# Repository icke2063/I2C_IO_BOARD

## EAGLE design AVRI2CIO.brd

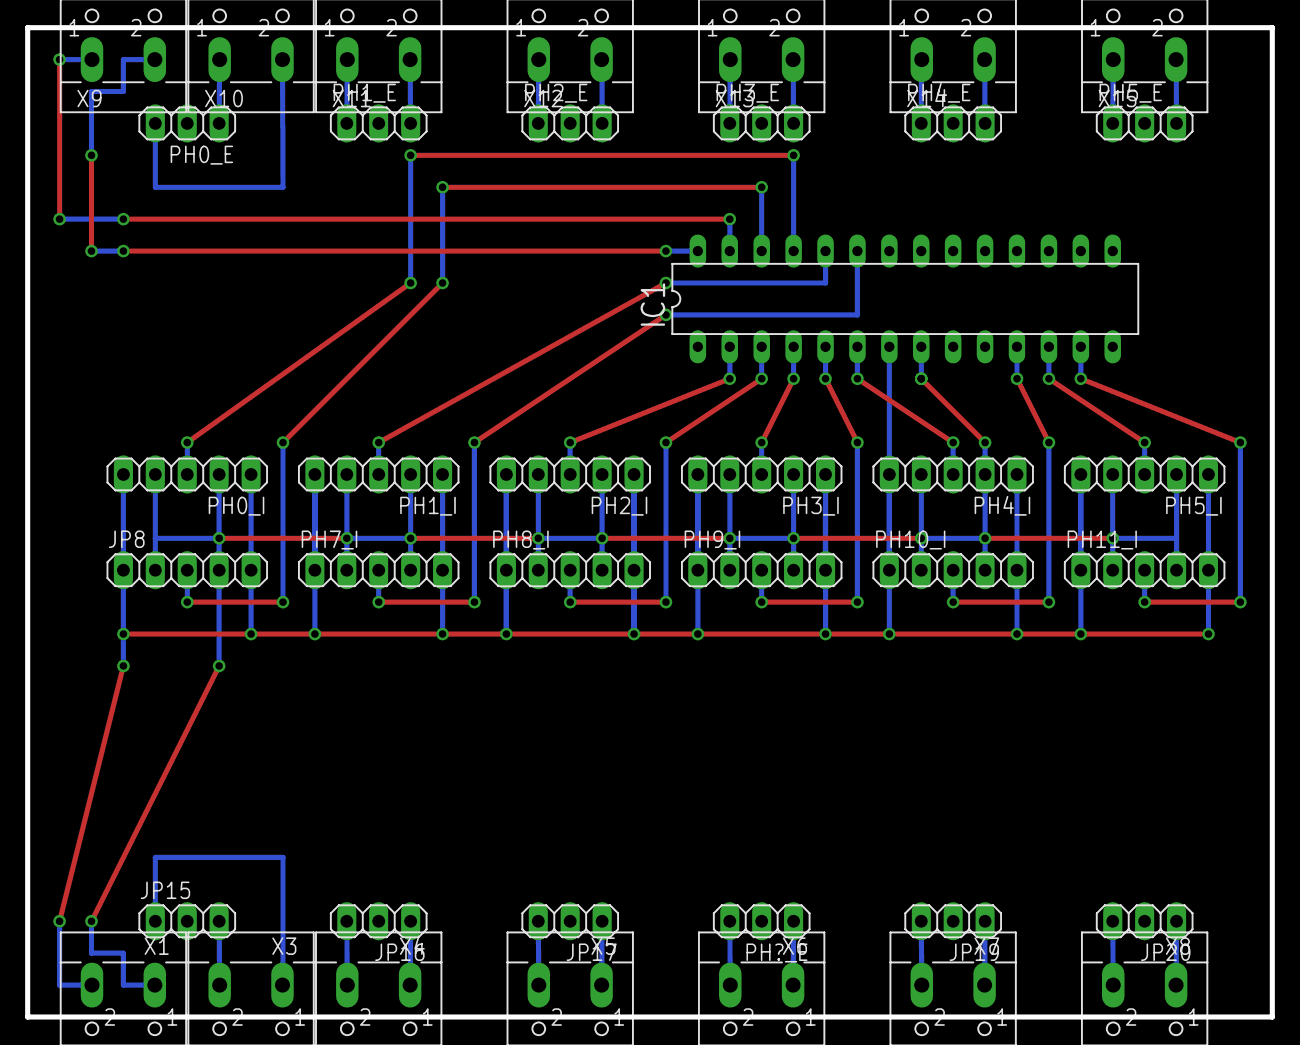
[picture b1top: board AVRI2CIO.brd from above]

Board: 2 copper layers, 99.1 x 78.7 mm, 39 parts (0 on the bottom side), 40 nets.

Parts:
IC1: MEGA8-P; DIL28-3
JP8: 1X05
JP15, JP16, JP17, JP19, JP20: 1X03
PH0_E, PH1_E, PH2_E, PH3_E, PH4_E, PH5_E: 1X03
PH0_I, PH1_I, PH2_I, PH3_I, PH4_I, PH5_I, PH7_I, PH8_I, PH9_I, PH10_I, PH11_I: 1X05
PH?_E: 1X03
X1, X3, X4, X5, X6, X7, X8, X9, X10, X11, X12, X13, X14, X15: W237-102

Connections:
+5V: IC1.7, JP8.1, JP8.5, PH0_I.1, PH0_I.5, PH1_I.1, PH1_I.5, PH2_I.1, PH2_I.5, PH3_I.1, PH3_I.5, PH4_I.1, PH4_I.5, PH5_I.1, PH5_I.5, PH7_I.1, PH7_I.5, PH8_I.1, PH8_I.5, PH9_I.1, PH9_I.5, PH10_I.1, PH10_I.5, PH11_I.1, PH11_I.5, X1.2
GND: IC1.8, JP8.2, JP8.4, PH0_I.2, PH0_I.4, PH1_I.2, PH1_I.4, PH2_I.2, PH2_I.4, PH3_I.2, PH3_I.4, PH4_I.2, PH4_I.4, PH5_I.2, PH5_I.4, PH7_I.2, PH7_I.4, PH8_I.2, PH8_I.4, PH9_I.2, PH9_I.4, PH10_I.2, PH10_I.4, PH11_I.2, PH11_I.4, X1.1
unnamed: PH0_E.3, X10.2
unnamed: JP15.3, X3.2
unnamed: JP15.1, X3.1
unnamed: JP16.3, X4.2
unnamed: JP16.1, X4.1
unnamed: JP17.3, X5.2
unnamed: JP17.1, X5.1
unnamed: PH?_E.3, X6.2
unnamed: PH?_E.1, X6.1
unnamed: JP19.3, X7.2
unnamed: JP19.1, X7.1
unnamed: JP20.3, X8.2
unnamed: JP20.1, X8.1
unnamed: PH0_E.1, X10.1
unnamed: PH1_E.1, X11.1
unnamed: PH1_E.3, X11.2
unnamed: PH2_E.1, X12.1
unnamed: PH2_E.3, X12.2
unnamed: PH3_E.1, X13.1
unnamed: PH3_E.3, X13.2
unnamed: PH4_E.1, X14.1
unnamed: PH4_E.3, X14.2
unnamed: PH5_E.1, X15.1
unnamed: PH5_E.3, X15.2
PC0: IC1.23, PH7_I.3
PC1: IC1.24, PH1_I.3
PC2: IC1.25, PH0_I.3
PC3: IC1.26, JP8.3
PD0: IC1.2, PH2_I.3
PD1: IC1.3, PH8_I.3
PD2: IC1.4, PH3_I.3
PD3: IC1.5, PH9_I.3
PD4: IC1.6, PH4_I.3
PD5: IC1.11, PH10_I.3
PD6: IC1.12, PH5_I.3
PD7: IC1.13, PH11_I.3
SCL: IC1.28, X9.2
SDA: IC1.27, X9.1

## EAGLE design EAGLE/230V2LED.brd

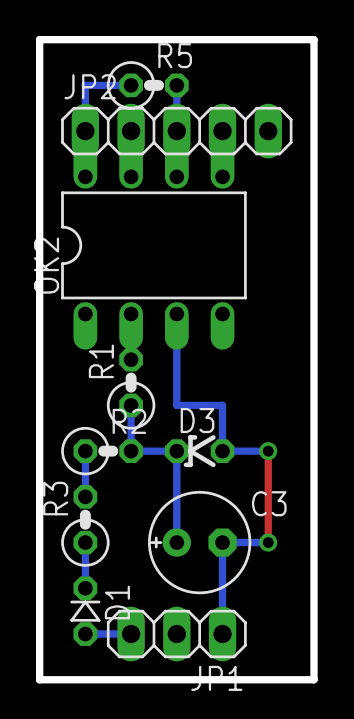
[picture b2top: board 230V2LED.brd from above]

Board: 2 copper layers, 15.2 x 35.6 mm, 10 parts (0 on the bottom side), 9 nets.

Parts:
C3: E2,5-6E
D1: D-2.5
D3: ZDIO-2.5
JP1: 1X03
JP2: 1X05
OK2: 6N138; DIL08
R1: 12K; 0207/2V
R2, R3: 22K; 0207/2V
R5: 0207/2V

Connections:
unnamed: JP2.1, OK2.8, R5.1
unnamed: JP2.4, OK2.5
unnamed: JP2.3, OK2.6, R5.2
unnamed: D1.C, R3.1
unnamed: R2.1, R3.2
unnamed: OK2.2, R1.2
unnamed: D1.A, JP1.3
unnamed: C3.-, D3.A, JP1.1, OK2.3
unnamed: C3.+, D3.C, R1.1, R2.2

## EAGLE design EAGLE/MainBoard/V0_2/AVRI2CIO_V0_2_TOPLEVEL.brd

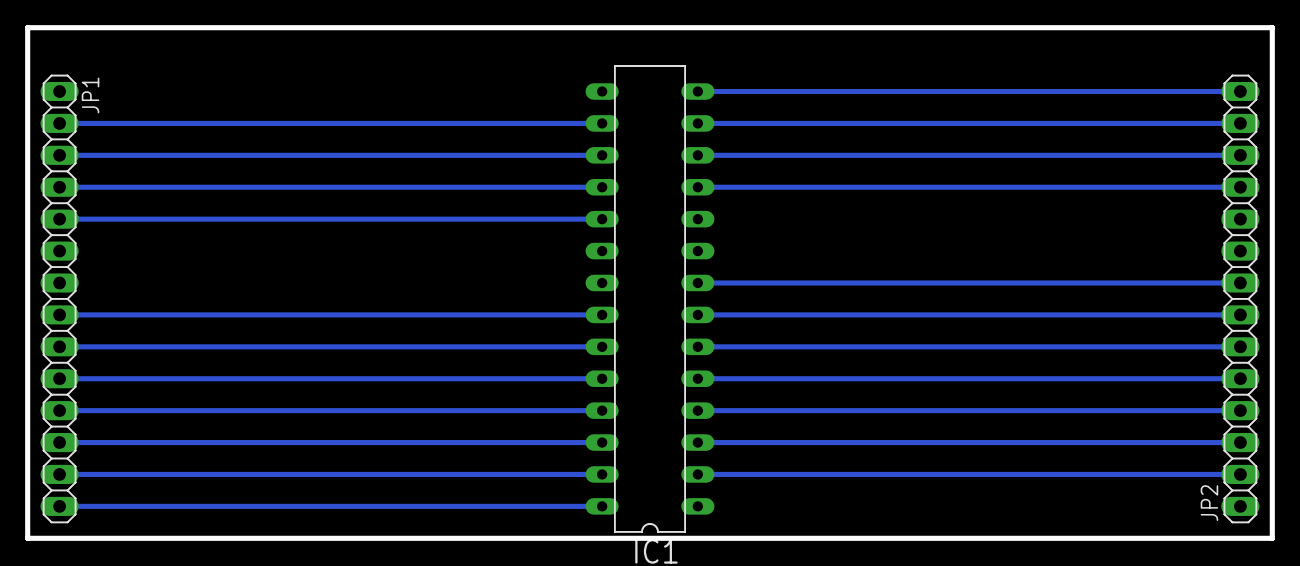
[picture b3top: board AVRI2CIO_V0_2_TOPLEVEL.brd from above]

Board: 2 copper layers, 99.1 x 40.6 mm, 3 parts (0 on the bottom side), 21 nets.

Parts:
IC1: MEGA8-P; DIL28-3
JP1, JP2: 1X14

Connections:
+5V: IC1.7, JP2.7
GND: IC1.8, IC1.22, JP1.8, JP2.8
PB0: IC1.14, JP2.14
PB2: IC1.16, JP1.2
PB3: IC1.17, JP1.3
PB4: IC1.18, JP1.4
PB5: IC1.19, JP1.5
PC0: IC1.23, JP1.9
PC1: IC1.24, JP1.10
PC2: IC1.25, JP1.11
PC3: IC1.26, JP1.12
PD0: IC1.2, JP2.2
PD1: IC1.3, JP2.3
PD2: IC1.4, JP2.4
PD3: IC1.5, JP2.5
PD4: IC1.6, JP2.6
PD5: IC1.11, JP2.11
PD6: IC1.12, JP2.12
PD7: IC1.13, JP2.13
SCL: IC1.28, JP1.14
SDA: IC1.27, JP1.13

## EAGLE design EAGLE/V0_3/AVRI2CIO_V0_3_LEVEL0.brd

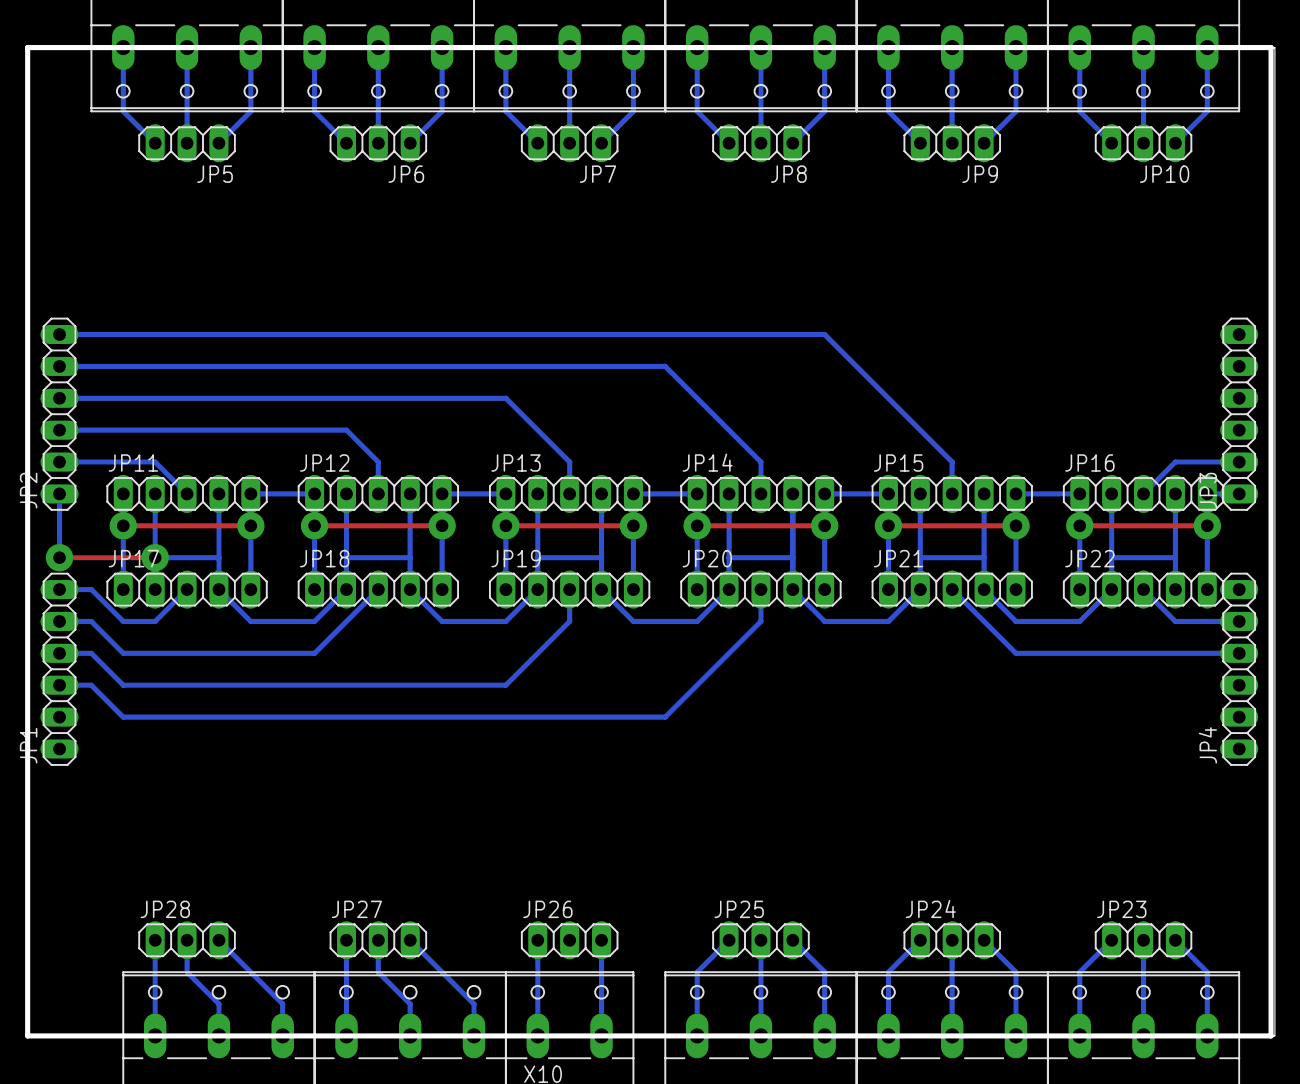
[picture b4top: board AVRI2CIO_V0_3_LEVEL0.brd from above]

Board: 2 copper layers, 99.4 x 78.7 mm, 40 parts (0 on the bottom side), 49 nets.

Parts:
JP1, JP2, JP3, JP4: 1X06
JP5, JP6, JP7, JP8, JP9, JP10, JP23, JP24, JP25, JP26, JP27, JP28: 1X03
JP11, JP12, JP13, JP14, JP15, JP16, JP17, JP18, JP19, JP20, JP21, JP22: 1X05
X1, X2, X3, X4, X5, X6, X7, X8, X9, X11, X12: W237-3E
X10: W237-132

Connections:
+5V: JP3.1, JP11.1, JP11.5, JP12.1, JP12.5, JP13.1, JP13.5, JP14.1, JP14.5, JP15.1, JP15.5, JP16.1, JP16.5, JP17.1, JP17.5, JP18.1, JP18.5, JP19.1, JP19.5, JP20.1, JP20.5, JP21.1, JP21.5, JP22.1, JP22.5
GND: JP2.1, JP11.2, JP11.4, JP12.2, JP12.4, JP13.2, JP13.4, JP14.2, JP14.4, JP15.2, JP15.4, JP16.2, JP16.4, JP17.2, JP17.4, JP18.2, JP18.4, JP19.2, JP19.4, JP20.2, JP20.4, JP21.2, JP21.4, JP22.2, JP22.4
unnamed: JP2.2, JP11.3
unnamed: JP2.3, JP12.3
unnamed: JP1.4, JP19.3
unnamed: JP2.4, JP13.3
unnamed: JP2.5, JP14.3
unnamed: JP2.6, JP15.3
unnamed: JP1.6, JP17.3
unnamed: JP1.5, JP18.3
unnamed: JP4.5, JP22.3
unnamed: JP4.4, JP21.3
unnamed: JP3.2, JP16.3
unnamed: JP1.3, JP20.3
unnamed: JP10.2, X6.2
unnamed: JP10.1, X6.1
unnamed: JP10.3, X6.3
unnamed: JP9.3, X5.3
unnamed: JP9.2, X5.2
unnamed: JP9.1, X5.1
unnamed: JP8.3, X4.3
unnamed: JP8.2, X4.2
unnamed: JP8.1, X4.1
unnamed: JP7.3, X3.3
unnamed: JP7.2, X3.2
unnamed: JP7.1, X3.1
unnamed: JP6.3, X2.3
unnamed: JP6.2, X2.2
unnamed: JP6.1, X2.1
unnamed: JP5.3, X1.3
unnamed: JP5.2, X1.2
unnamed: JP5.1, X1.1
unnamed: JP28.3, X12.3
unnamed: JP28.2, X12.2
unnamed: JP28.1, X12.1
unnamed: JP27.3, X11.3
unnamed: JP27.2, X11.2
unnamed: JP27.1, X11.1
unnamed: JP25.3, X9.3
unnamed: JP25.2, X9.2
unnamed: JP25.1, X9.1
unnamed: JP24.3, X8.3
unnamed: JP24.2, X8.2
unnamed: JP24.1, X8.1
unnamed: JP23.3, X7.3
unnamed: JP23.2, X7.2
unnamed: JP23.1, X7.1
unnamed: JP26.1, X10.1
unnamed: JP26.3, X10.2
